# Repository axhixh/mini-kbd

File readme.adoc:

= Mini Keyboard

This is my experiment with https://ergogen.xyz[Ergogen] and building
a keyboard from scratch.

I had a bunch of https://www.waveshare.com/wiki/RP2040-Zero[RP2040 Zero]
microcontrollers and Choc Mini switches to play with. Even though I am
used to 34 keys, https://github.com/axhixh/haigha-mod[Haigha Mod], and 
use it as my daily driver, I decided to build one with 36 keys because
I can do that without using diodes.

== Choc v1 vs Choc mini

While I did design this keyboard to play with Choc mini switches, I did
create a Choc v1 version since it was easy with Ergogen and I wanted to
see how to make reversible, hot-swappable PCB.

The Choc mini version of the PCB is in link:choc-mini[] and the Choc v1
version is in link:choc-v1[].

image:images/choc-mini-pcb.png[Using Choc mini switches]

image:images/choc-v1-pcb.png[Using Choc v1 swithes]

== TRRS vs 4 pin mini DIN 

Inspired by the https://github.com/etiennecollin/wave[Wave Keyboard],
I redesigned the keyboard to use 4 pin mini DIN used by S-video to
protect the microcontroller from
https://docs.qmk.fm/#/feature_split_keyboard?id=considerations[accidentally shorting].
The layout of the key switches is the same between the different keyboards,
the connection between the two halves is the only difference.

== Releases

Please download the latest gerber files for the key switch you need from
https://github.com/axhixh/mini-kbd/releases[Releases]

Remember PCB thickness of 1.6mm for Choc mini means the pins will not pass
through the hole. I was fine with this since I use don't use a case. 

PCB for Choc mini keyboard using 4 pin mini-DIN for connecting the halves.
image:images/pcb_using_4_pin_din.jpg[Photo of PCB]

PCBs for Choc mini and Choc v1 using TRRS.
image:images/pcbs.jpg[Photo of PCBs]

Built out keyboard with Choc mini.
image:images/right_half.jpg[Right Half]
image:images/keyboard_4_pin_din.jpg[Two halves with S-video cable]
 
Built out keyboard with Choc Sunset and LDSA keycaps.
image:images/mini-kbd.jpg[Photo of keyboard]

== Firmware

The `firmware` folder contains different firmwares for the board.
Currently, it supports https://kmkfw.io[KMK] and https://docs.qmk.fm[QMK]

== References

While creating design I used https://github.com/mitxela/kicad-round-tracks[round-track]
plug-in.

The RP2040 Zero footprint is a modified version of https://github.com/CountParadox/RP2040-Zero-Kicad.
A possible improvement for future is to change it to have the origin in the center so
that rotating the footprint is easier.

The footprint for 4 pin mini-DIN is based on the one used in Wave keyboard.
I translated it to Ergogen footprint.

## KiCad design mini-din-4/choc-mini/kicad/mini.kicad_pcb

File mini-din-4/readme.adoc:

= Mini Keyboard

The keyboards under this directory use 4 pin mini DIN connectors
instead of TRRS to connect the two half.

Reference:

https://github.com/etiennecollin/wave[Wave Keyboard]

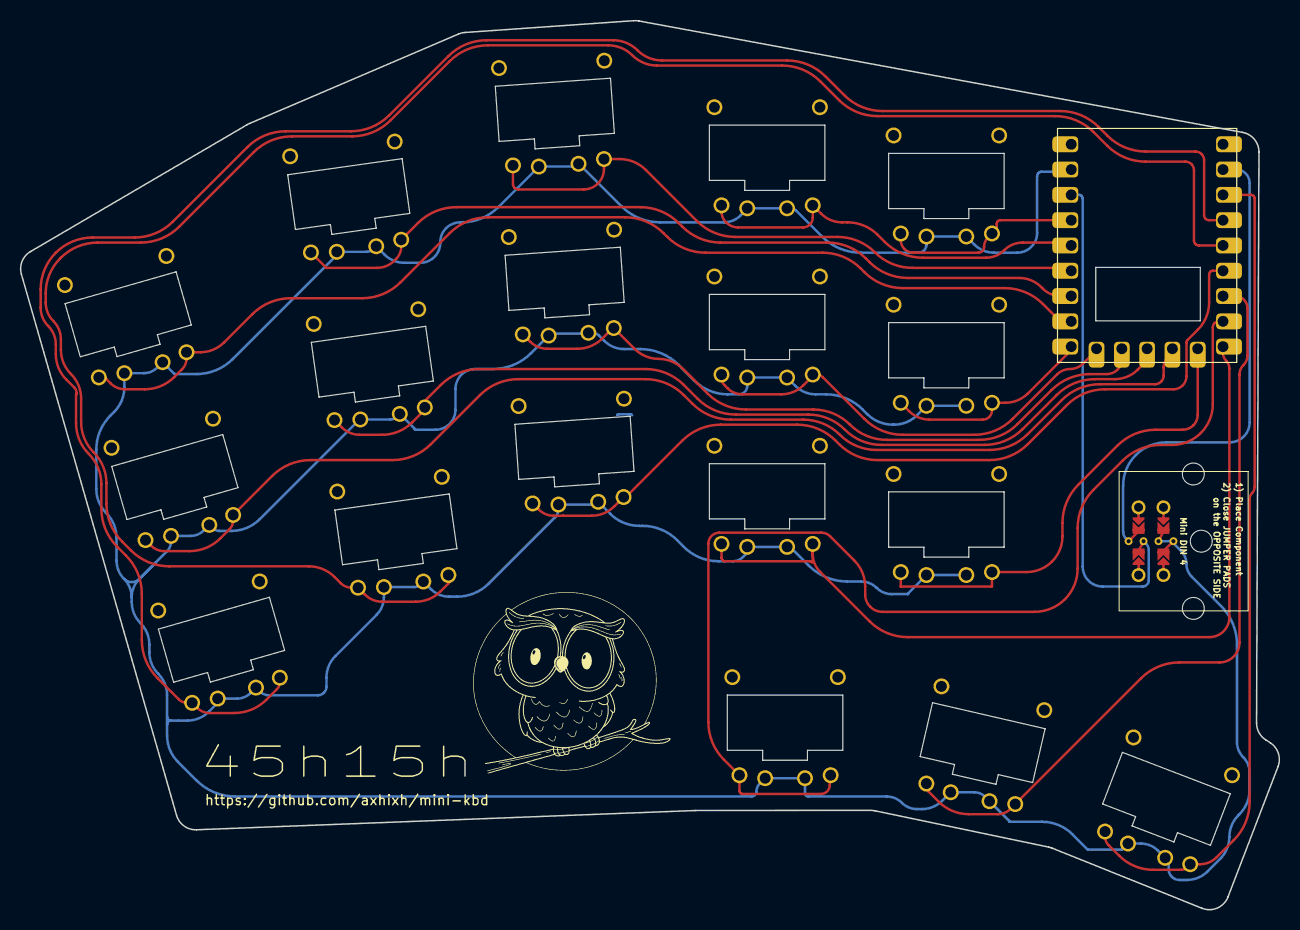
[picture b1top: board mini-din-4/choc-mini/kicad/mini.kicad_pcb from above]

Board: 2 copper layers, 126.4 x 89.3 mm, 22 parts (1 on the bottom side), 21 nets.

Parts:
AdamTech-MDJ004FS1: MiniDIN4; AdamTech_MDJ-004-FS_reversible
LOGO1, LOGO2: LOGO
RP2040Zero1: RP2040-Zero
S1, S2, S3, S4, S5, S6, S7, S8, S9, S10, S11, S12, S13, S14, S15, S16, S17, S18: Kailh_PG1232

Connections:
GND: AdamTech-MDJ004FS1.3, AdamTech-MDJ004FS1.5, RP2040Zero1.20, S1.2, S2.2, S3.2, S4.2, S5.2, S6.2, S7.2, S8.2, S9.2, S10.2, S11.2, S12.2, S13.2, S14.2, S15.2, S16.2, S17.2, S18.2
GP1: AdamTech-MDJ004FS1.8, RP2040Zero1.2
GP2: RP2040Zero1.3, S18.1
GP3: RP2040Zero1.4, S1.1
GP4: RP2040Zero1.5, S4.1
GP5: RP2040Zero1.6, S7.1
GP6: RP2040Zero1.7, S17.1
GP7: RP2040Zero1.8, S16.1
GP8: RP2040Zero1.9, S10.1
GP9: RP2040Zero1.10, S13.1
GP10: RP2040Zero1.11, S2.1
GP11: RP2040Zero1.12, S5.1
GP12: RP2040Zero1.13, S8.1
GP13: RP2040Zero1.14, S11.1
GP14: RP2040Zero1.15, S14.1
GP15: RP2040Zero1.16, S3.1
GP26: RP2040Zero1.17, S6.1
GP27: RP2040Zero1.18, S9.1
GP28: RP2040Zero1.22, S12.1
GP29: RP2040Zero1.23, S15.1
P3V3: AdamTech-MDJ004FS1.6, RP2040Zero1.21

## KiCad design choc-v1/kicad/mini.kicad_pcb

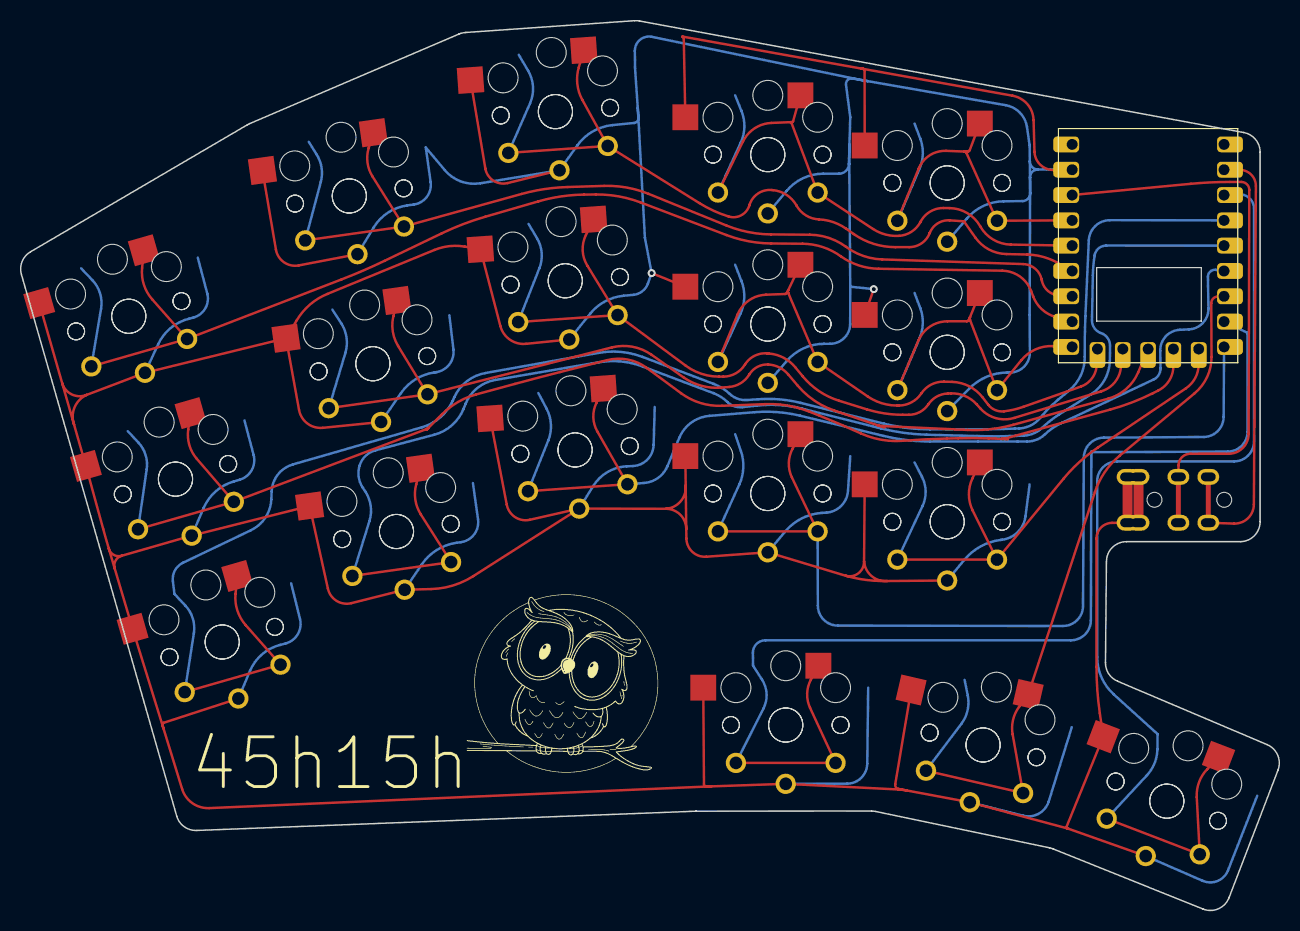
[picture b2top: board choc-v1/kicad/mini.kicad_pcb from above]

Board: 2 copper layers, 126.3 x 89.3 mm, 38 parts (0 on the bottom side), 21 nets.

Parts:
RP2040Zero1: RP2040-Zero
S1, S2, S3, S4, S5, S6, S7, S8, S9, S10, S11, S12, S13, S14, S15, S16, S17, S18, S19, S20, S21, S22, S23, S24, S25, S26, S27, S28, S29, S30, S31, S32, S33, S34, S35, S36: PG1350
TRRS1: TRRS-PJ-320A-dual

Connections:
GND: RP2040Zero1.20, S1.2, S2.2, S3.2, S4.2, S5.2, S6.2, S7.2, S8.2, S9.2, S10.2, S11.2, S12.2, S13.2, S14.2, S15.2, S16.2, S17.2, S18.2, S19.2, S20.2, S21.2, S22.2, S23.2, S24.2, S25.2, S26.2, S27.2, S28.2, S29.2, S30.2, S31.2, S32.2, S33.2, S34.2, S35.2, S36.2, TRRS1.1, TRRS1.2
GP1: RP2040Zero1.2, TRRS1.4
GP2: RP2040Zero1.3, S18.1, S36.1
GP3: RP2040Zero1.4, S1.1, S19.1
GP4: RP2040Zero1.5, S4.1, S22.1
GP5: RP2040Zero1.6, S7.1, S25.1
GP6: RP2040Zero1.7, S17.1, S35.1
GP7: RP2040Zero1.8, S16.1, S34.1
GP8: RP2040Zero1.9, S10.1, S28.1
GP9: RP2040Zero1.10, S13.1, S31.1
GP10: RP2040Zero1.11, S2.1, S20.1
GP11: RP2040Zero1.12, S5.1, S23.1
GP12: RP2040Zero1.13, S8.1, S26.1
GP13: RP2040Zero1.14, S11.1, S29.1
GP14: RP2040Zero1.15, S14.1, S32.1
GP15: RP2040Zero1.16, S3.1, S21.1
GP26: RP2040Zero1.17, S6.1, S24.1
GP27: RP2040Zero1.18, S9.1, S27.1
GP28: RP2040Zero1.22, S12.1, S30.1
GP29: RP2040Zero1.23, S15.1, S33.1
P3V3: RP2040Zero1.21, TRRS1.3

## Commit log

2023-05-15 release 1 of mini
2023-05-15 info about gerber files
2023-05-15 ignore kicad backups
2023-05-15 add more clearance to 3.3v route
2023-05-15 add pcb images
2023-05-22 ignore release gerber zip files
2023-06-10 initial implementation of firmware with kmk
2023-06-10 update readme for firmware
2023-06-10 add photos
2023-06-11 fix media keys for kmk
2023-06-13 changed key layout
2023-06-13 stop mounting the microcontroller as a drive
2023-07-18 changed window manager keys
2023-08-15 make reset switch each layer consistent
2023-09-05 ignore macos files
2023-12-30 wip using 4pin mini-din
2024-01-07 working footprint for 4 pin mini din
2024-01-07 remove kicad footprint
2024-01-07 clean up to footprint
2024-01-07 remove kicad models
2024-01-07 footprint for 4pin mini din socket
2024-01-08 add logo icon
2024-01-08 add logo icon (#2)
2024-01-08 add footprint for text
2024-01-08 added comment about changes
2024-01-08 support footprint to add custom text (#3)
    * add footprint for text
    * added comment about changes
2024-01-08 add new keyboard based on mini din connector
2024-02-02 updated with photos of keyboard of 4 pin mini-din
2024-02-02 keymap updated to support aerospace window manager
2024-02-02 top-level readme has the details
2024-02-02 add comment about pcb thickness
2024-02-02 updated license
2024-02-02 add qmk files
2024-02-02 remove keymap json file
2024-02-02 remove temp files
2024-02-02 add keyboard based on mini 4 pin DIN (#4)
    * add new keyboard based on mini din connector
    * updated with photos of keyboard of 4 pin mini-din
    * keymap updated to support aerospace window manager
    * updated license
    * add qmk files
2024-08-31 ignore ergogen generated files
